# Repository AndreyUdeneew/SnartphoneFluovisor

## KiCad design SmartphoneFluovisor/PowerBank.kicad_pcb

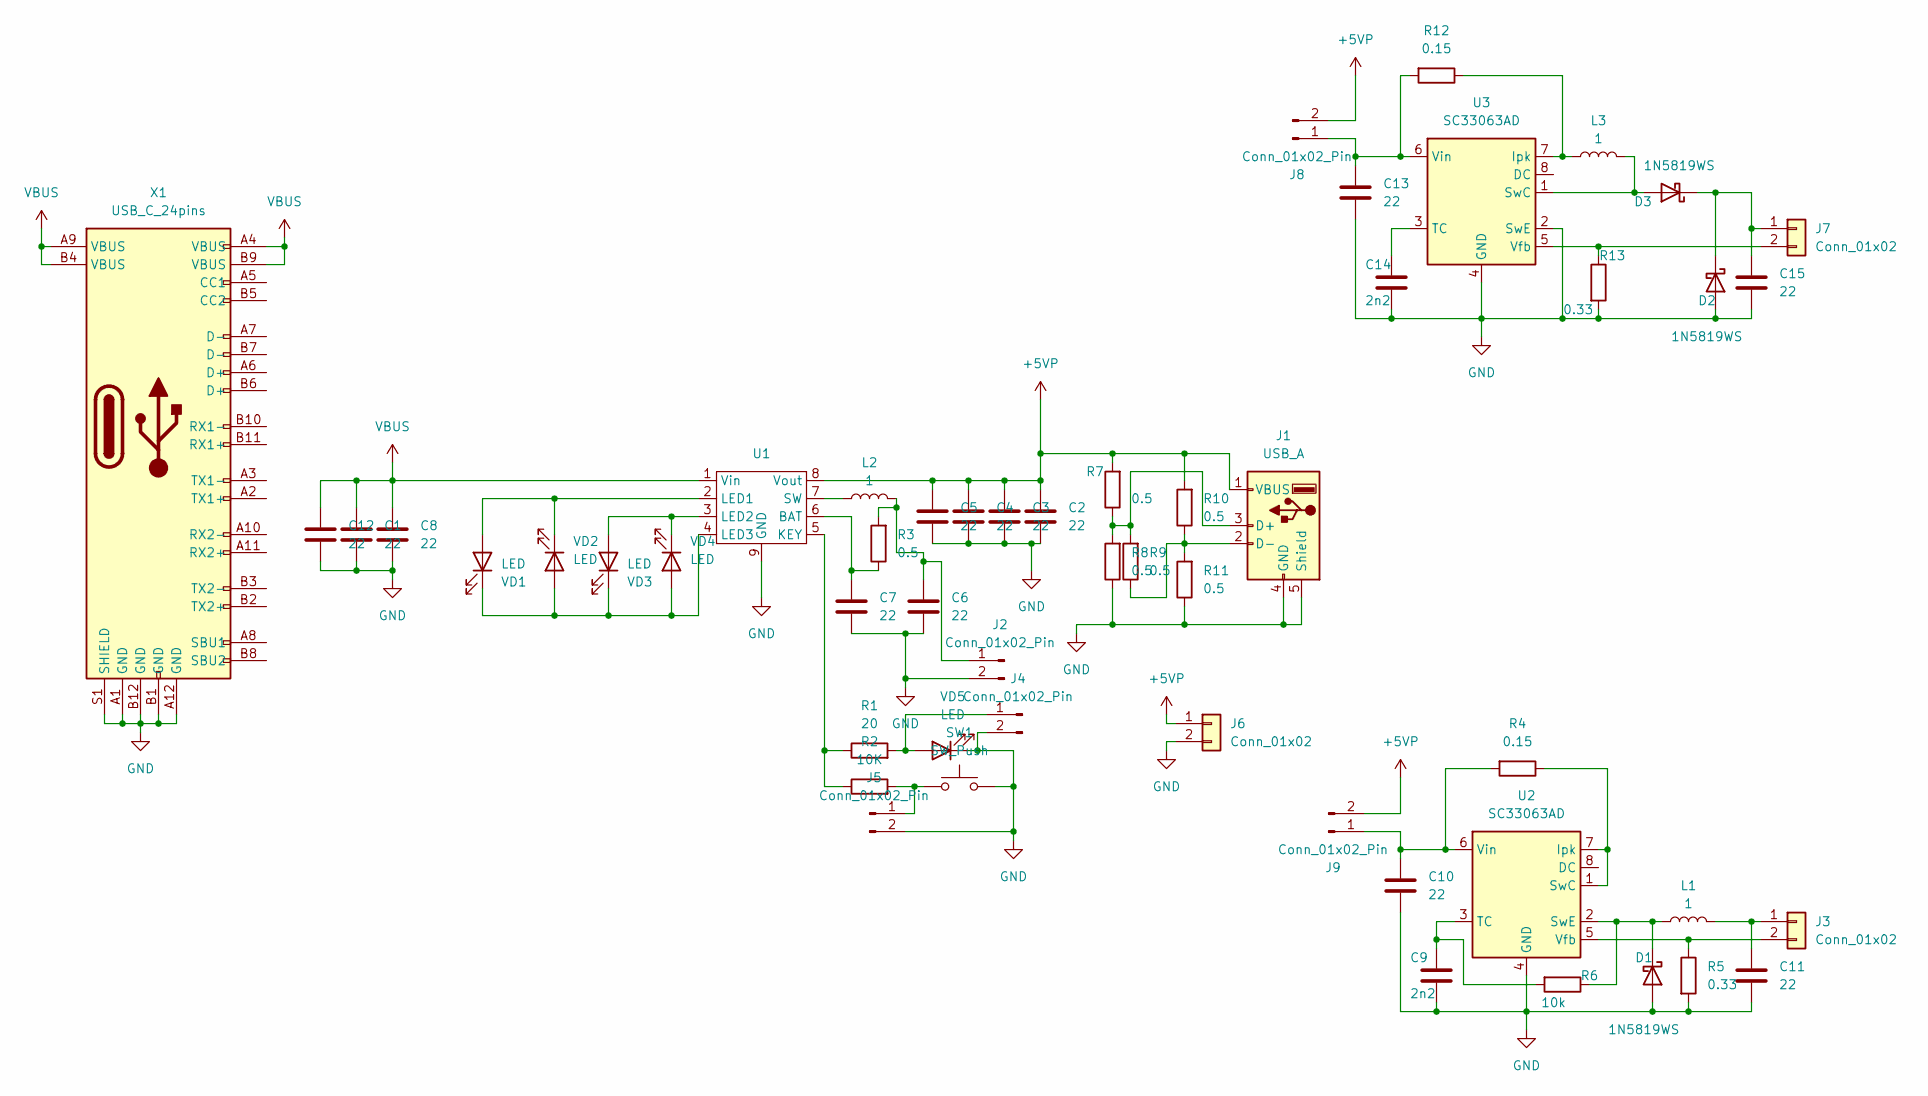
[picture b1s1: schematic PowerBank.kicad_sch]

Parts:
C1, C2, C3, C4, C5, C6, C7, C8, C10, C11, C12, C13, C15: 22; C_1206_3216Metric_Pad1.33x1.80mm_HandSolder
C9, C14: 2n2; C_0603_1608Metric_Pad1.08x0.95mm_HandSolder
D1, D2, D3: 1N5819WS; D_SOD-323_HandSoldering
J1: USB_A; USB_A_Molex_67643_Horizontal
J2, J4, J5, J8, J9: Conn_01x02_Pin; PinHeader_1x02_P2.54mm_Vertical
J3, J6, J7: Conn_01x02; PinHeader_1x02_P2.54mm_Vertical
L1, L3: 1; L_12x12mm_H8mm
L2: 1; L_Vishay_IHLP-2525
R1: 20; R_0603_1608Metric_Pad0.98x0.95mm_HandSolder
R2: 10K; R_0603_1608Metric_Pad0.98x0.95mm_HandSolder
R3, R7, R8, R9, R10, R11: 0.5; R_0603_1608Metric_Pad0.98x0.95mm_HandSolder
R4: 0.15; R_0603_1608Metric_Pad0.98x0.95mm_HandSolder
R5, R13: 0.33; R_1206_3216Metric_Pad1.30x1.75mm_HandSolder
R6: 10k; R_0603_1608Metric_Pad0.98x0.95mm_HandSolder
R12: 0.15; R_1206_3216Metric_Pad1.30x1.75mm_HandSolder
SW1: SW_Push; PinHeader_1x02_P2.54mm_Vertical
U1: HSOP-8-1EP_3.9x4.9mm_P1.27mm_EP2.41x3.1mm_ThermalVias
U2, U3: SC33063AD; SOIC-8_3.9x4.9mm_P1.27mm
VD1, VD2, VD3, VD4: LED; LED_0805_2012Metric_Pad1.15x1.40mm_HandSolder
VD5: LED; LED_0603_1608Metric_Pad1.05x0.95mm_HandSolder
X1: USB_C_24pins; FPC_12

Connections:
+5VP: C2.1, C3.1, C4.1, C5.1, J1.1 (VBUS), J6.1, J8.2, J9.2, R7.2, R10.2, U1.8 (Vout)
GND: C1.2, C2.2, C3.2, C4.2, C5.2, C6.2, C7.2, C8.2, C9.2, C10.2, C11.2, C12.2, C13.2, C14.2, C15.2, D1.2 (A), D2.2 (A), J1.4 (GND), J1.5 (Shield), J2.2, J4.2, J5.2, J6.2, R5.2, R8.1, R11.1, R13.2, SW1.2, U1.9 (GND), U2.4 (GND), U3.2 (SwE), U3.4 (GND), VD5.1 (K), X1.A1 (GND), X1.A12 (GND), X1.B1 (GND), X1.B12 (GND), X1.S1 (SHIELD), X1.S2 (SHIELD), X1.S3 (SHIELD), X1.S4 (SHIELD)
unnamed: D1.1 (K), L1.1, R6.1, U2.2 (SwE)
unnamed: C15.1, D2.1 (K), D3.1 (K), J7.1
unnamed: D3.2 (A), L3.2, U3.1 (SwC)
unnamed: J1.3 (D+), R7.1, R8.2, R9.2
unnamed: J1.2 (D-), R9.1, R10.1, R11.2
unnamed: C6.1, J2.1, L2.2, R3.2
unnamed: C11.1, J3.1, L1.2
unnamed: J3.2, R5.1, U2.5 (Vfb)
unnamed: J4.1, R1.2, VD5.2 (A)
unnamed: J5.1, R2.2, SW1.1
unnamed: J7.2, R13.1, U3.5 (Vfb)
unnamed: C13.1, J8.1, R12.2, U3.6 (Vin)
unnamed: C10.1, J9.1, R4.2, U2.6 (Vin)
unnamed: C7.1, R3.1, U1.6 (BAT)
unnamed: R1.1, R2.1, U1.5 (KEY)
unnamed: U1.2 (LED1), VD1.2 (A), VD2.1 (K)
unnamed: U1.3 (LED2), VD3.2 (A), VD4.1 (K)
unnamed: U1.4 (LED3), VD1.1 (K), VD2.2 (A), VD3.1 (K), VD4.2 (A)
unnamed: L2.1, U1.7 (SW)
unnamed: R4.1, U2.1 (SwC), U2.7 (Ipk)
unnamed: C9.1, R6.2, U2.3 (TC)
unnamed: L3.1, R12.1, U3.7 (Ipk)
unnamed: C14.1, U3.3 (TC)
VBUS: C1.1, C8.1, C12.1, U1.1 (Vin), X1.A4 (VBUS), X1.A9 (VBUS), X1.B4 (VBUS), X1.B9 (VBUS)

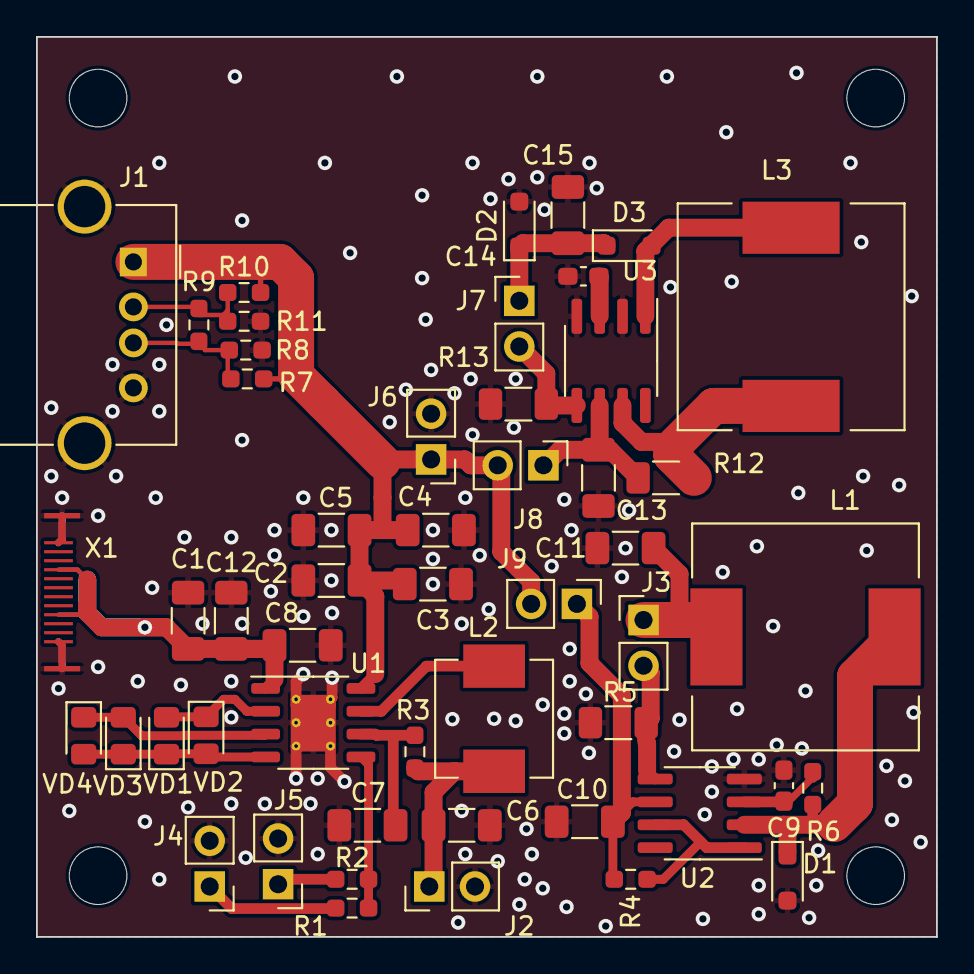
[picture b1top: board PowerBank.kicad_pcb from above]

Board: 2 copper layers, 50.0 x 50.0 mm, 51 parts (0 on the bottom side), 26 nets.

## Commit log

2023-12-31 v0.1 Blank files were added
2024-01-02 v0.2 First iteration of Circuit and PCB
2024-01-21 v0.3 connectors are on the same side
2024-01-21 v0.4 Seems 2B ready
2024-02-04 v0.5 proto of boost driver was added
2024-02-05 v0.6 Circuit was completed, boost driver components were added onto PCB
2024-02-05 v0.7 boost & buck driver are added into the PCB. Seems 2B ready!
